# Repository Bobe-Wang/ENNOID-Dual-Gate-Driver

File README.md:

# ENNOID - Dual Gate Driver

The "Dual Gate Driver" can be directly connected to this control board:

https://github.com/paltatech/VESC-controller

The driver is pin compatible with several power modules such as the ones listed below:

- http://www.mitsubishielectric.com/semiconductors/content/product/powermod/powmod/igbtmod/tgatef/cm300du-12f_e.pdf
- https://www.wolfspeed.com/cas120m12bm2

## V0.1 (untested & archived):

V0.1 is based upon the design from wolfspeed two-channel gate driver for 1200V SiC MOSFET power modules
- https://www.wolfspeed.com/cgd15hb62p1

Feature:

- Dual gate driver
- 2W Isolated power supply / gate
- Direct mount low inductance design
- Short circuit protection
- Under voltage protection

Changes from the original wolfspeed design:

- Added Voltage sense circuit (Experimental)
- 98 x 60 mm 2 layer PCB made with Kicad
- Current sensor connector
- Temperature sensor circuit & connector
- Minimum SMD 0805 components size for easy handsoldering
- 2x8 (16) pins headers for easy connection with VESC board

## V0.2:

V0.2 is based upon the design from tiduc70a.pdf.

- http://www.ti.com/lit/ug/tiduc70a/tiduc70a.pdf

Changes from V0.1 include:

- BJT based powerstage instead of mosfet IC IXD-609
- Adjustable soft turnoff feature
- SMD gate resistor instead of MELF
- Active clamping / Over voltage protection
- Shoot trough EMI protection on PWM input

BOM link for 3 boards at Mouser below : 
- https://www.mouser.com/ProjectManager/ProjectDetail.aspx?AccessID=f6574b98ce

### Schematics

### Top View

### Bottom View

### Board View

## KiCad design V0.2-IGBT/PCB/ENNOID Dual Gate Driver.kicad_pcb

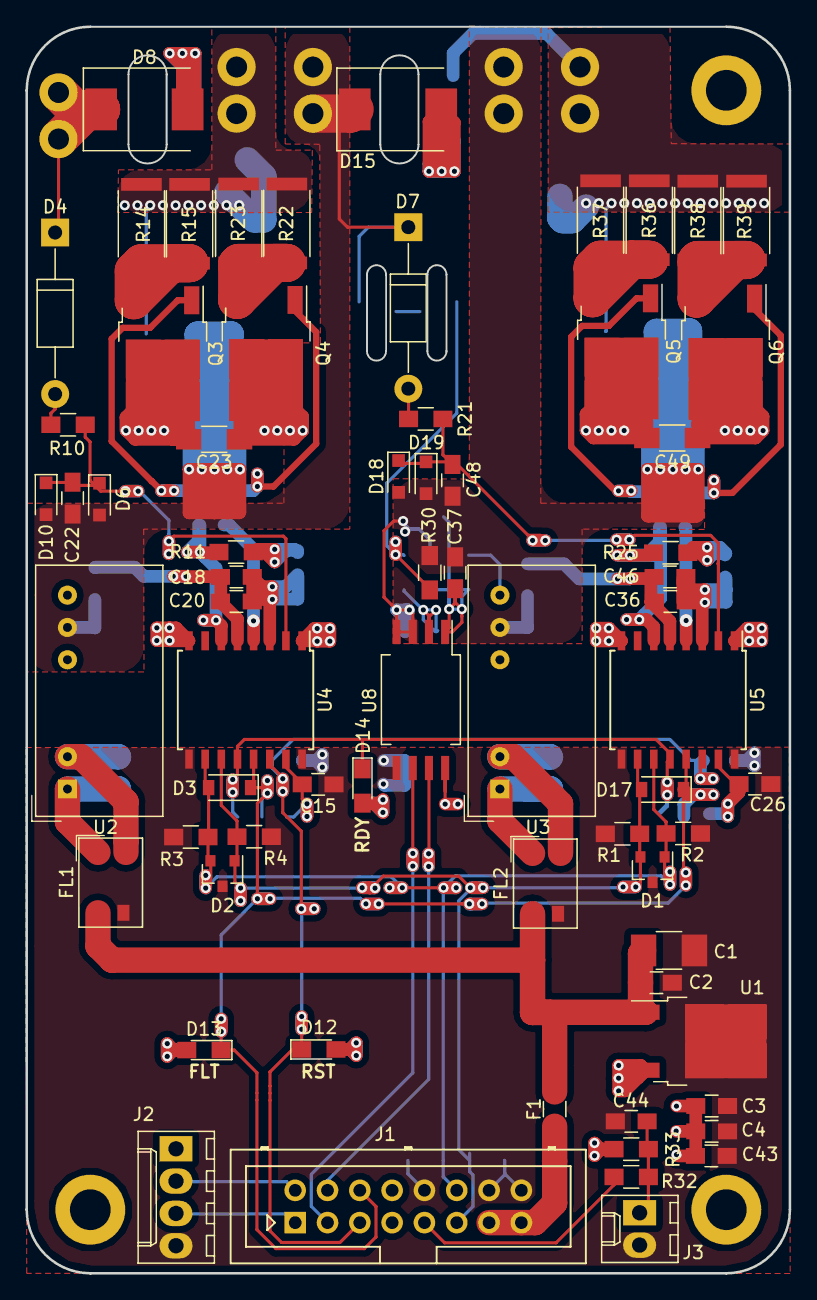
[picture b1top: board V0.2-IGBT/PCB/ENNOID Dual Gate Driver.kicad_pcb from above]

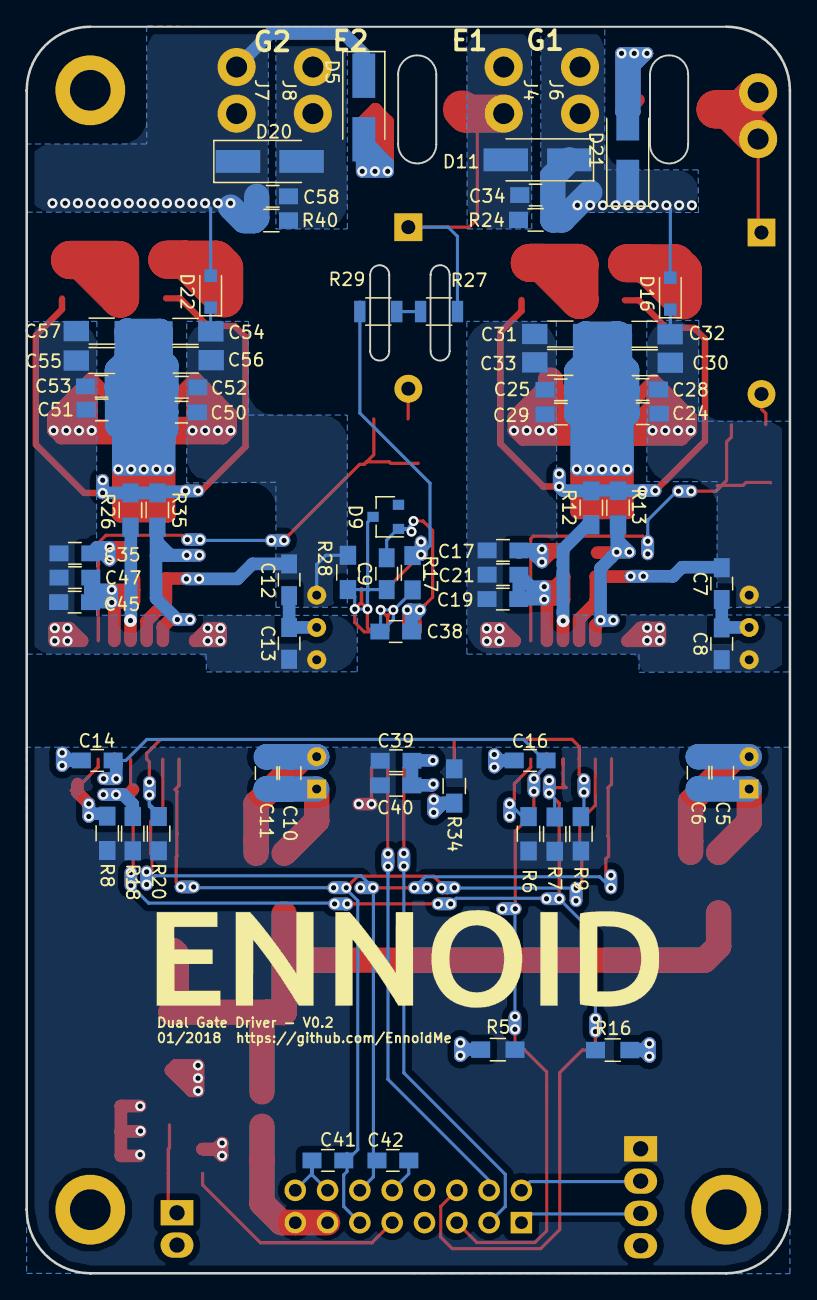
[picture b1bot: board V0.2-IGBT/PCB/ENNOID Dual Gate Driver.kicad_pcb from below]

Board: 2 copper layers, 60.0 x 98.0 mm, 142 parts (71 on the bottom side), 57 nets.

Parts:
C1: 10u; C_1210_HandSoldering
C2, C3, C5, C10, C14, C15, C16, C18, C19, C24, C25, C26, C36, C37, C39, C41, C42, C45, C50, C51: 100n; C_0805_HandSoldering
C4, C6, C7, C8, C11, C12, C13, C20, C21, C28, C29, C43, C44, C46, C47, C52, C53: 1u; C_0805_HandSoldering
C9: 10u; C_0805_HandSoldering
C17, C35: 15n; C_0805_HandSoldering
C22, C48: 220p; C_0805_HandSoldering
C23, C30, C31, C32, C33, C49, C54, C55, C56, C57: 10u; C_1206_HandSoldering
C34, C58: 0.22u; C_0805_HandSoldering
C38: 330p; C_0805_HandSoldering
C40: 2.2u; C_0805_HandSoldering
D1, D2: GSOT03C; SOT-23
D3, D17: 1N4148W; D_SOD-123
D4, D7: sTth112; D_DO-41_SOD81_P12.70mm_Horizontal
D5, D21: es2j-ltp; D_SMA_Handsoldering
D6, D18: MMSZ5242BS; D_SOD-323_HandSoldering
D8, D15: smcj440ca; D_SMC
D9: 5V; D_SOT-23_ANK
D10, D19: BAT54WS-7-F; D_SOD-323_HandSoldering
D11, D20: SMAJ18CA; D_SMA_Handsoldering
D12, D13, D14: LED; LED_0805_HandSoldering
D16, D22: PMEG4010; D_SOD-323_HandSoldering
F1: Fuse; R_0805_HandSoldering
FL1, FL2: ACM4520
G1: Logo_ENNOID; ENNOID-LOGO
J1: Conn_02x08_Odd_Even; Multicomp_MC9A12-1634_2x08x2.54mm_Straight
J2: Current; Molex_KK-6410-04_04x2.54mm_Straight
J3: TEMP; Molex_KK-6410-02_02x2.54mm_Straight
J4: PHASE; Quick_fit_terminal
J5: Collector; Quick_fit_terminal
J6: Gate_H; Quick_fit_terminal
J7: G_L; Quick_fit_terminal
J8: E; Quick_fit_terminal
J9: Mounting hole 1; MountingHole_3.2mm_M3_ISO14580_Pad
J10: Mounting Hole 2; MountingHole_3.2mm_M3_ISO14580_Pad
J11: Mounting Hole 3; MountingHole_3.2mm_M3_ISO14580_Pad
Q3, Q5: MJD3055T4G; TO-252-2
Q4, Q6: MJD2955T4G; TO-252-2
R1, R3: 4.7k; R_0805_HandSoldering
R2, R4, R10, R21, R30: 1k; R_0805_HandSoldering
R5, R16, R34: 300; R_0805_HandSoldering
R6, R8, R17: 10; R_0805_HandSoldering
R7, R9, R18, R20, R24, R40: 10k; R_0805_HandSoldering
R11, R12, R13, R25, R26, R35: 12; R_0805_HandSoldering
R14, R15, R22, R23, R36, R37, R38, R39: 3; R_2512
R27, R29: 1M; R_1206
R28: 800; R_0805_HandSoldering
R32, R33: R; R_0805_HandSoldering
U1: MC7805; TO-252-2
U2, U3: MGJ2; DCDC-Conv_muRata_MGJ2
U4, U5: ISO5852SDWR; SOIC-16W_7.5x10.3mm_Pitch1.27mm
U8: AMC1301; SSO-8_6.8x5.9mm_Pitch1.27mm_Clearance8mm

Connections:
+5V: C3.1, C4.1, C39.1, C40.1, C43.1, J2.1, R5.1, R6.2, R7.1, R8.2, R9.1, R16.1, R18.1, R20.1, R33.1, R34.1, U1.3, U8.8
+24V: C1.1, C2.1, F1.2, FL1.1, FL2.1, U1.1
/GD_HIGH/+VCC: C7.1, C18.1, C20.1, C23.1, C24.1, C28.1, C30.1, C32.1, D16.1, Q3.2, U2.7, U4.5
/GD_HIGH/-VEE: C8.2, C17.2, C19.2, C21.2, C23.2, C25.2, C29.2, C31.2, C33.2, Q4.2, U2.5, U4.1, U4.8
/GD_HIGH/C: D4.1, D8.1, J5.1
/GD_HIGH/G: C34.1, D11.1, D16.2, D21.1, J6.1, R14.1, R15.1, R22.1, R23.1, R24.2
/GD_LOW/+VCC: C12.1, C36.1, C46.1, C49.1, C50.1, C52.1, C54.1, C56.1, D22.1, Q5.2, R28.2, U3.7, U5.5
/GD_LOW/-VEE: C13.2, C35.2, C45.2, C47.2, C49.2, C51.2, C53.2, C55.2, C57.2, Q6.2, U3.5, U5.1, U5.8
/GD_LOW/G: C58.1, D5.1, D20.1, D22.2, J7.1, R36.1, R37.1, R38.1, R39.1, R40.2
/ISO_PSU_LOW/COM: C9.2, C12.2, C13.1, C37.2, C38.2, C48.2, C50.2, C51.1, C52.2, C53.1, C54.2, C55.1, C56.2, C57.1, C58.2, D9.2, D18.2, D19.2, D20.2, J8.1, R30.1, R40.1, U3.6, U8.3, U8.4
FLT: D3.1, D13.1, D17.1, J1.6, R7.2, R18.2, U4.13, U5.13
GND: C1.2, C2.2, C3.2, C4.2, C14.2, C15.1, C16.2, C26.1, C39.2, C40.2, C41.2, C42.2, C43.2, C44.2, D1.3, D2.3, FL1.2, FL2.2, J1.10, J1.14, J1.16, J2.4, J3.2, R1.2, R2.2, R3.2, R4.2, U1.2, U4.9, U4.16, U5.9, U5.16, U8.5
I+: J1.2, J2.2
I-: J1.1, J2.3
unnamed: C5.1, C6.1, FL1.4, U2.1
unnamed: C5.2, C6.2, FL1.3, U2.2
unnamed: C10.1, C11.1, FL2.4, U3.1
unnamed: C10.2, C11.2, FL2.3, U3.2
unnamed: C15.2, R6.1, U4.15
unnamed: C17.1, R11.1
unnamed: C18.2, C19.1, C20.2, C21.1, U4.3
unnamed: C22.1, D6.1, D10.1, R10.2, U4.2
unnamed: C26.2, R8.1, U5.15
unnamed: C35.1, R25.1
unnamed: C36.2, C45.1, C46.2, C47.1, U5.3
unnamed: C9.1, C37.1, D9.1, R28.1, U8.1
unnamed: C38.1, R17.2, U8.2
unnamed: C44.1, J3.1, R32.1, R33.2
unnamed: C48.1, D18.1, D19.1, R21.2, U5.2
unnamed: D4.2, R10.1
unnamed: D7.2, R21.1
unnamed: D12.2, R5.2
unnamed: D13.2, R16.2
unnamed: D14.2, R34.2
unnamed: D5.2, D15.2
unnamed: D8.2, D21.2
unnamed: F1.1, J1.13, J1.15
unnamed: Q3.1, Q4.1, R12.1, R13.1
unnamed: Q3.3, R14.2, R15.2
unnamed: Q4.3, R22.2, R23.2
unnamed: Q5.1, Q6.1, R26.1, R35.1
unnamed: Q5.3, R36.2, R37.2
unnamed: Q6.3, R38.2, R39.2
unnamed: R11.2, R13.2, U4.6
unnamed: R12.2, U4.4
unnamed: R17.1, R29.1, R30.2
unnamed: R25.2, R35.2, U5.6
unnamed: R26.2, U5.4
unnamed: R27.1, R29.2
PHASE: C7.2, C8.1, C22.2, C24.2, C25.1, C28.2, C29.1, C30.2, C31.1, C32.2, C33.1, C34.2, D6.2, D7.1, D10.2, D11.2, D15.1, J4.1, R24.1, R27.2, U2.6
PWM_H: C42.1, D1.1, D2.2, D3.2, J1.12, R2.1, R3.1, U4.10, U5.11
PWM_L: C41.1, D1.2, D2.1, D17.2, J1.11, R1.1, R4.1, U4.11, U5.10
RDY: D14.1, R9.2, R20.2, U4.12, U5.12
RST: C14.1, C16.1, D12.1, J1.5, U4.14, U5.14
TEMP: J1.9, R32.2
Vout+: J1.4, U8.7
Vout-: J1.3, U8.6

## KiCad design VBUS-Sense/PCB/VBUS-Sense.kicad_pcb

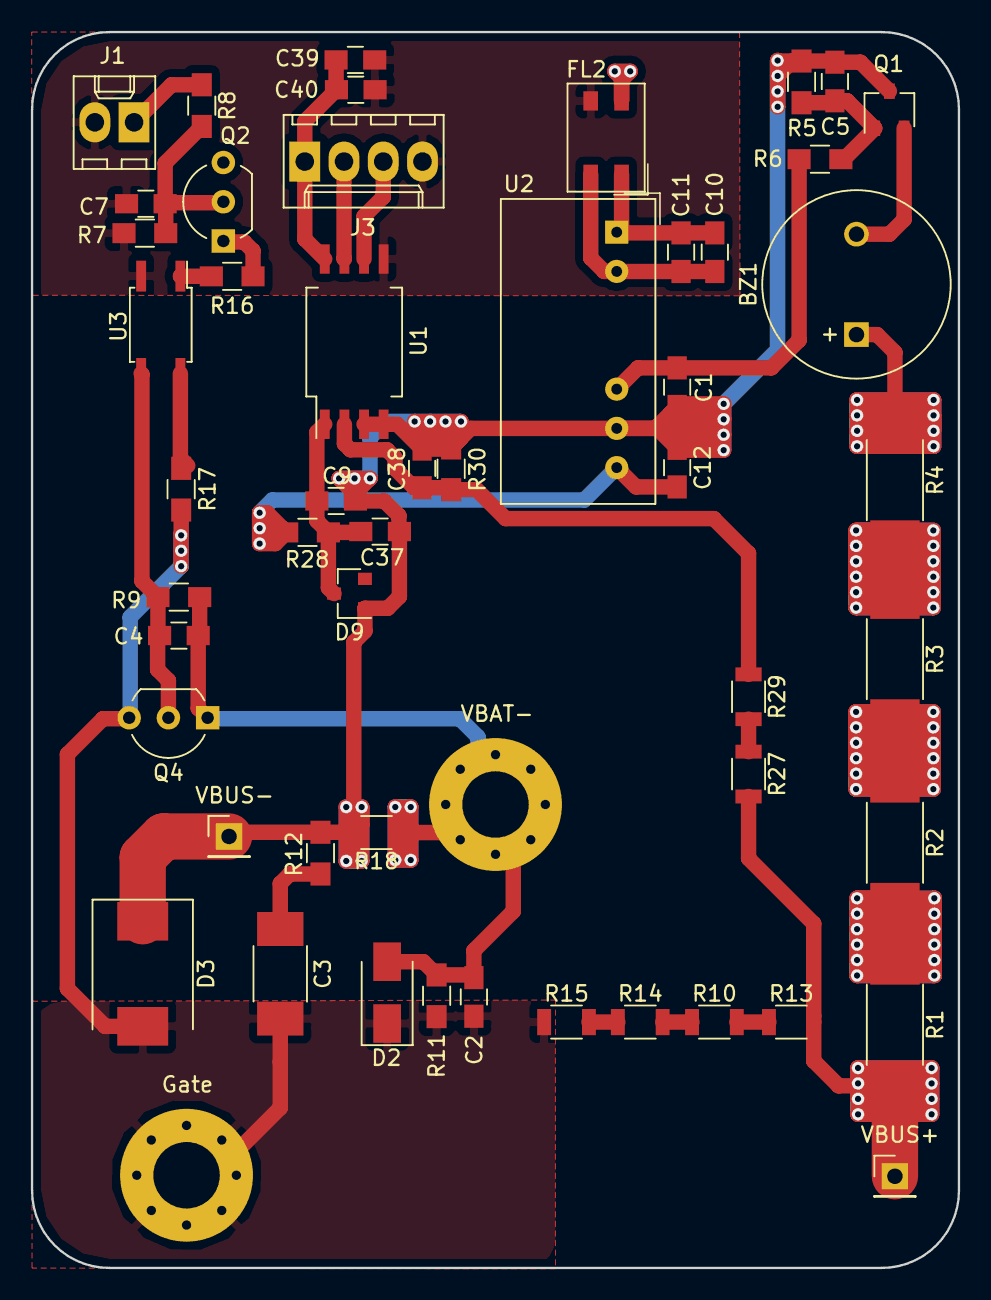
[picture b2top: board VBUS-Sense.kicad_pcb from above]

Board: 2 copper layers, 60.0 x 80.0 mm, 54 parts (1 on the bottom side), 31 nets.

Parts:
BZ1: Buzzer; MagneticBuzzer_ProSignal_ABT-410-RC
C1, C11, C12: 1u; C_0805_HandSoldering
C2: 0.15u; C_0805_HandSoldering
C3: 0.15u; C_1812_HandSoldering
C4, C5, C7, C10, C37, C39: 100n; C_0805_HandSoldering
C9: 10u; C_0805_HandSoldering
C38: 330p; C_0805_HandSoldering
C40: 2.2u; C_0805_HandSoldering
D2: D_Zener 18V SMAJ18CA; D_SMA
D3: D_Zener 440v SMJC440CA; D_SMC
D9: 5V; D_SOT-23_ANK
FL2: ACM4520
J1: Conn_01x02 to external 12V power switch or VESC G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; Molex_KK-6410-02_02x2.54mm_Straight
J3: Conn_01x04 to vesc board; Molex_KK-6410-04_04x2.54mm_Straight
LOGO1: Logo_ENNOID; ENNOID-LOGO
MK1: VBUS-; Pin_Header_Straight_1x01_Pitch2.54mm
MK2: VBUS+; Pin_Header_Straight_1x01_Pitch2.54mm
MK3: Gate; MountingHole_4.3mm_M4_Pad_Via
MK4: VBAT-; MountingHole_4.3mm_M4_Pad_Via
Q1: Depletion mode FET ex: CPC3982; SOT-23W
Q2, Q4: 2N7000; TO-92_Inline_Wide
R1, R2, R3, R4: 7.5K; R_2512_HandSoldering
R5: 20k; R_0805_HandSoldering
R6: 100; R_0805_HandSoldering
R7: 1M; R_0805_HandSoldering
R8, R12, R16, R17, R30: 1k; R_0805_HandSoldering
R9: 10k; R_0805_HandSoldering
R10, R13, R14, R15, R18: 200k; R_1206
R11: 30k; R_0805_HandSoldering
R27, R29: 1M; R_1206
R28: 800; R_0805_HandSoldering
U1: AMC1301; SSO-8_6.8x5.9mm_Pitch1.27mm_Clearance8mm
U2: MGJ2; DCDC-Conv_muRata_MGJ2
U3: LTV-356T; SO-4_4.4x3.6mm_Pitch2.54mm

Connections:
+5V: C39.1, C40.1, FL2.1, J3.1, Q2.3, U1.8
/ISO_PSU/+VCC: C12.1, R28.2, U2.7
/ISO_PSU/-VEE: C1.2, R6.2, U2.5
/ISO_PSU/COM: C1.1, C5.2, C9.2, C12.2, C37.2, C38.2, D3.1, D9.2, MK1.1, Q1.3, R5.1, R12.1, R18.2, R30.1, U1.3, U1.4, U2.6
/Inrush_Limiter/+VBUS: MK2.1, R1.2, R13.2, R27.2
/Inrush_Limiter/GATE: C2.1, C3.2, D2.1, D3.2, MK3.1, Q4.3, R11.2, R15.1, R17.2
/Inrush_Limiter/ON/OFF: J1.1, R8.2
/Inrush_Limiter/VBAT-: C2.2, C4.2, D2.2, MK4.1, Q4.1, R9.1, R11.1, R18.1
/V_BUS/Vout+: J3.2, U1.7
/V_BUS/Vout-: J3.3, U1.6
GND: C7.2, C39.2, C40.2, FL2.2, J1.2, J3.4, R7.2, U1.5, U3.2
unnamed: BZ1.1, R4.1
unnamed: BZ1.2, Q1.2
unnamed: C3.1, R12.2
unnamed: C4.1, Q4.2, R9.2, U3.3
unnamed: C5.1, Q1.1, R5.2, R6.1
unnamed: C7.1, Q2.2, R7.1, R8.1
unnamed: C10.1, C11.1, FL2.4, U2.1
unnamed: C10.2, C11.2, FL2.3, U2.2
unnamed: C9.1, C37.1, D9.1, R28.1, U1.1
unnamed: C38.1, R29.1, R30.2, U1.2
unnamed: Q2.1, R16.2
unnamed: R1.1, R2.2
unnamed: R2.1, R3.2
unnamed: R3.1, R4.2
unnamed: R10.1, R14.2
unnamed: R10.2, R13.1
unnamed: R14.1, R15.2
unnamed: R16.1, U3.1
unnamed: R17.1, U3.4
unnamed: R27.1, R29.2

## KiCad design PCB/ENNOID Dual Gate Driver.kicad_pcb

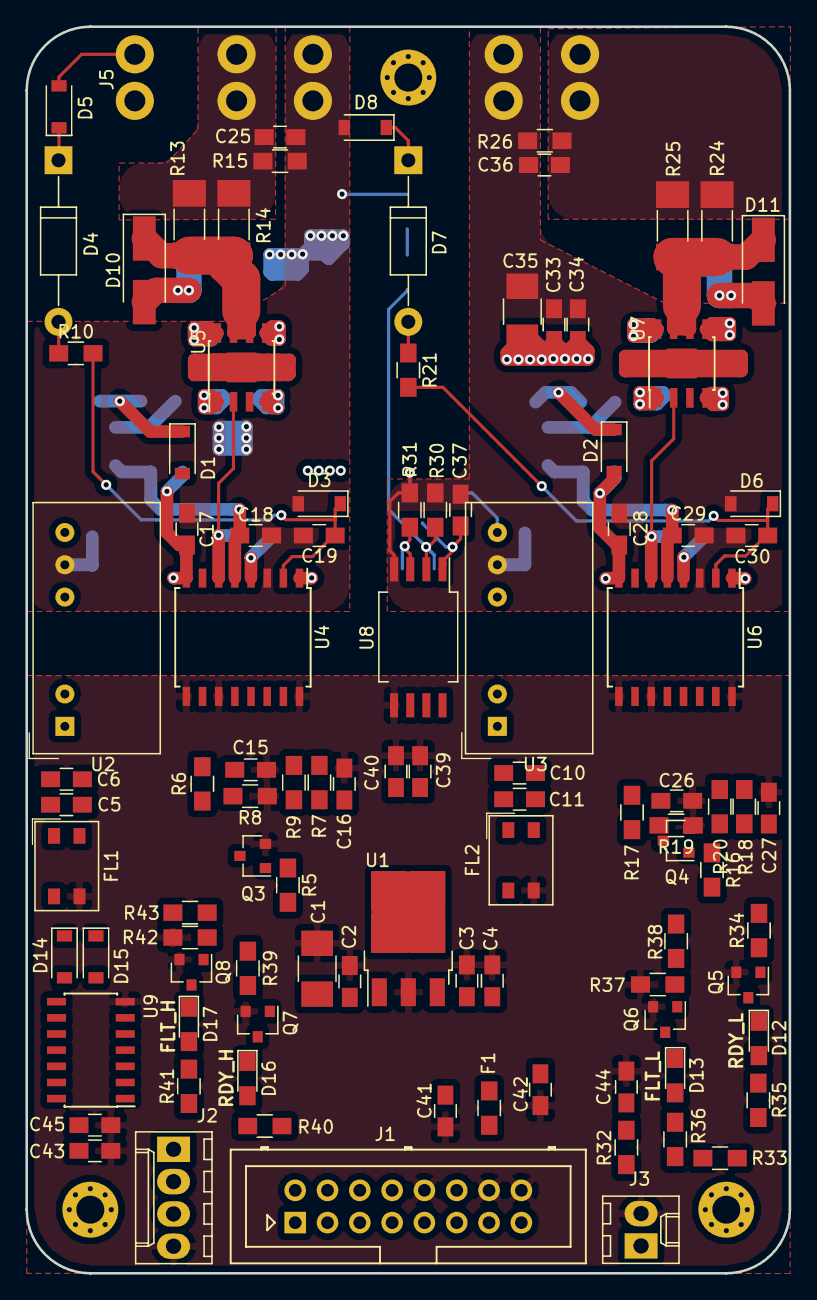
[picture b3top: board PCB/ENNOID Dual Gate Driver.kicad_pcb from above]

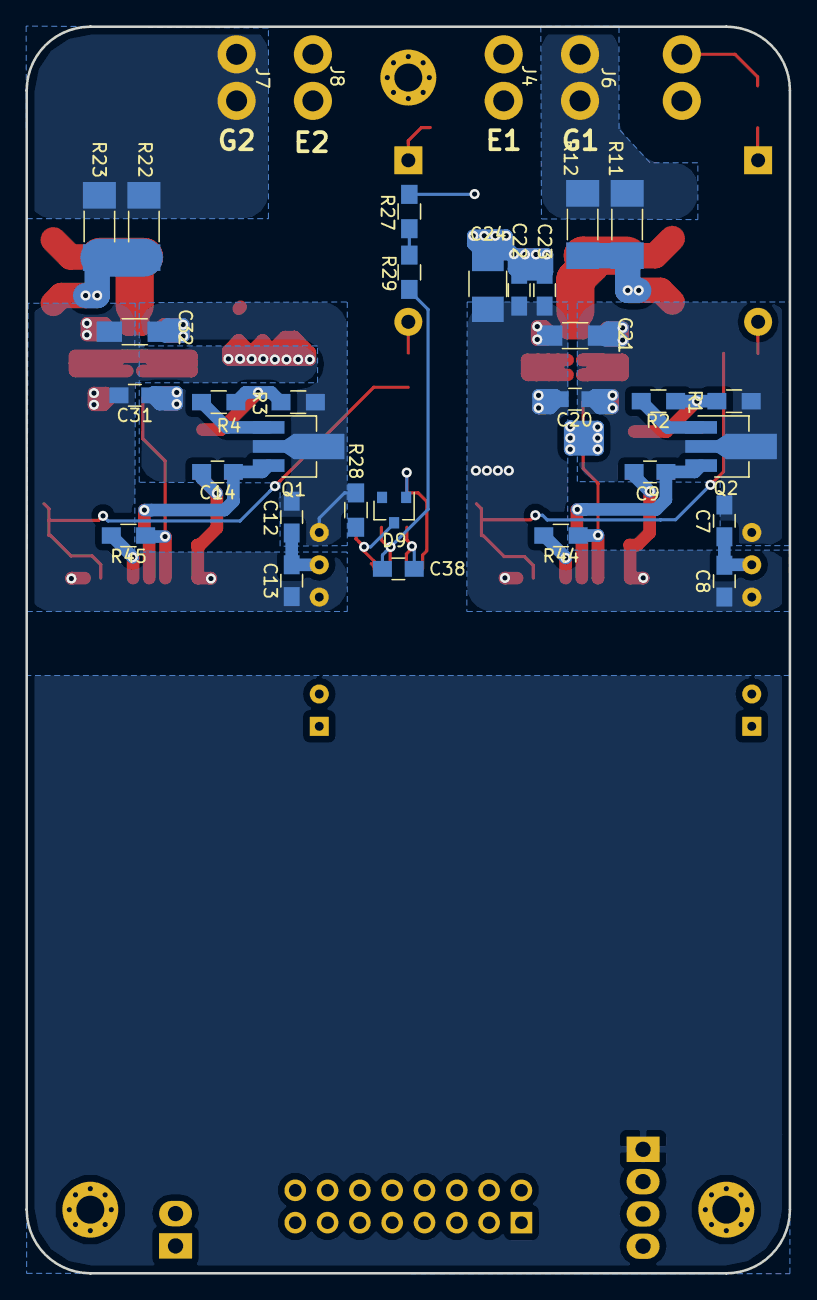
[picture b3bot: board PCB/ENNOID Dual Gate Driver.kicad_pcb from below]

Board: 2 copper layers, 60.0 x 98.0 mm, 138 parts (34 on the bottom side), 75 nets.

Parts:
C1: 10u; C_1210_HandSoldering
C2, C3, C5, C10, C15, C16, C17, C18, C20, C23, C26, C27, C28, C29, C31, C34, C37, C39, C41, C42, C45: 100n; C_0805_HandSoldering
C4, C6, C7, C8, C9, C11, C12, C13, C14, C43, C44: 1u; C_0805_HandSoldering
C19, C25, C30, C36: DNP; C_0805_HandSoldering
C21, C32: 4.7u; C_1206_HandSoldering
C22, C33: 10n; C_0805_HandSoldering
C24, C35: 10u; R_1210_HandSoldering
C38: 330p; C_0805_HandSoldering
C40: 2.2u; C_0805_HandSoldering
D1, D2: MMSZ5251B; D_SOD-123
D3, D5, D6, D8: D_Zener; D_SOD-123
D4, D7: D; D_DO-41_SOD81_P12.70mm_Horizontal
D9: 5V; D_SOT-23_ANK
D10, D11: D; D_SMA_Handsoldering
D12, D13, D16, D17: LED; LED_0805_HandSoldering
D14, D15: B140HW; D_SOD-123
F1: Fuse; R_0805_HandSoldering
FL1, FL2: ACM4520
J1: Conn_02x08_Odd_Even; Multicomp_MC9A12-1634_2x08x2.54mm_Straight
J2: Current; Molex_KK-6410-04_04x2.54mm_Straight
J3: TEMP; Molex_KK-6410-02_02x2.54mm_Straight
J4: PHASE; Quick_fit_terminal
J5: Collector; Quick_fit_terminal
J6: Gate_H; Quick_fit_terminal
J7: G_L; Quick_fit_terminal
J8: E; Quick_fit_terminal
M1, M2, M3: MountingHole_2.2mm_M2_Pad_Via
Q1, Q2: Q_NPN_BCE; SOT-89-3_Handsoldering
Q3, Q4: 2N7002K-7; SOT-23
Q5, Q6, Q7, Q8: 2N7002; SOT-23
R1, R3, R7, R9, R10, R18, R20, R21, R37, R42: 10k; R_0805_HandSoldering
R2, R4: 0; R_0805_HandSoldering
R5, R6, R16, R17, R30, R31: 1k; R_0805_HandSoldering
R8, R15, R19, R26: 47k; R_0805_HandSoldering
R11, R12, R22, R23: DND; R_MELF_MMB-0207
R13, R14, R24, R25: 20; R_MELF_MMB-0207
R27, R29: 1M; R_0805_HandSoldering
R28: 200; R_0805_HandSoldering
R32, R33: R; R_0805_HandSoldering
R34, R39: 4.12k10; R_0805_HandSoldering
R35, R36, R40, R41: 4.12k; R_0805_HandSoldering
R38, R43: 10; R_0805_HandSoldering
R44, R45: DNP; R_0805_HandSoldering
U1: MC7805; TO-252-3_TabPin2
U2, U3: MGJ2; DCDC-Conv_muRata_MGJ2
U4, U6: 1ED020I12-F2; SOIC-16W_7.5x10.3mm_Pitch1.27mm
U5, U7: IXD-609; SOIC-8-1EP_3.9x4.9mm_Pitch1.27mm
U8: AMC1301; SSO-8_6.8x5.9mm_Pitch1.27mm_Clearance8mm
U9: 4069; SOIC-14_3.9x8.7mm_Pitch1.27mm

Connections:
+5V: C3.1, C4.1, C16.1, C27.1, C39.1, C40.1, C43.1, C45.1, J2.1, R7.1, R9.1, R18.1, R20.1, R33.1, U1.3, U4.15, U6.15, U8.8, U9.14
/GD_HIGH/+VCC: C7.1, C20.1, C21.1, Q2.2, R1.2, U2.7, U5.1, U5.8
/GD_HIGH/-VEE: C8.2, C9.2, C17.1, C20.2, C21.2, C22.2, C23.2, C24.2, D1.2, U2.5, U4.1, U4.8, U5.4, U5.5
/GD_HIGH/C: D5.2, J5.1
/GD_HIGH/G: C25.1, J6.1, R11.2, R12.2, R13.2, R14.2, R15.1
/GD_HIGH/VCC_REG: C9.1, C18.2, Q2.3, U4.5
/GD_LOW/+VCC: C12.1, C31.1, C32.1, Q1.2, R3.2, R28.2, U3.7, U7.1, U7.8
/GD_LOW/-VEE: C13.2, C14.2, C28.1, C31.2, C32.2, C33.2, C34.2, C35.2, D2.2, U3.5, U6.1, U6.8, U7.4, U7.5
/GD_LOW/E: C12.2, C13.1, C28.2, C29.1, C30.2, C33.1, C34.1, C35.1, C36.2, C37.2, D6.2, D9.2, J8.1, R26.2, R30.1, R31.1, U3.6, U6.3, U8.4
/GD_LOW/G: C36.1, J7.1, R22.2, R23.2, R24.2, R25.2, R26.1
/GD_LOW/VCC_REG: C14.1, C29.2, Q1.3, U6.5
FLT_ALL: D14.1, D15.1, J1.6, R5.2, R16.2
FLT_H: R7.2, U4.13, U9.3, U9.9
FLT_L: R18.2, U6.13, U9.1, U9.5
GND: C1.2, C2.2, C3.2, C4.2, C15.2, C16.2, C26.2, C27.2, C39.2, C40.2, C41.2, C42.2, C43.2, C44.2, C45.2, FL1.2, FL2.2, J1.10, J1.14, J1.16, J2.4, J3.2, Q3.2, Q4.2, Q5.2, Q6.2, Q7.2, Q8.2, R8.1, R19.1, R37.1, R42.1, U1.2, U4.9, U4.11, U4.16, U6.9, U6.11, U6.16, U8.5, U9.7
I+: J1.2, J2.2
I-: J1.1, J2.3
unnamed: C5.1, C6.1, FL1.4, U2.1
unnamed: C5.2, C6.2, FL1.3, U2.2
unnamed: C10.1, C11.1, FL2.4, U3.1
unnamed: C10.2, C11.2, FL2.3, U3.2
unnamed: C15.1, Q3.3, R6.1, R8.2, U4.10
unnamed: C19.1, D3.1, R10.2, U4.2
unnamed: C26.1, Q4.3, R17.1, R19.2, U6.10
unnamed: C30.1, D6.1, R21.2, U6.2
unnamed: C37.1, D9.1, R28.1, U8.1
unnamed: C38.1, R29.1, R30.2, U8.2
unnamed: C38.2, R31.2, U8.3
unnamed: C44.1, J3.1, R32.1, R33.2
unnamed: D1.1, R1.1, R2.1
unnamed: D2.1, R3.1, R4.1
unnamed: D4.1, D5.1
unnamed: D4.2, R10.1
unnamed: D7.1, D8.1
unnamed: D7.2, R21.1
unnamed: D10.1, R13.1, R14.1, U5.6, U5.7
unnamed: D10.2, R11.1, R12.1
unnamed: D11.1, R24.1, R25.1, U7.6, U7.7
unnamed: D11.2, R22.1, R23.1
unnamed: D12.1, Q5.3
unnamed: D12.2, R35.2
unnamed: D13.1, Q6.3
unnamed: D13.2, R36.2
unnamed: D14.2, U9.8
unnamed: D15.2, U9.6
unnamed: D16.1, Q7.3
unnamed: D16.2, R40.2
unnamed: D17.1, Q8.3
unnamed: D17.2, R41.2
unnamed: F1.1, J1.13, J1.15
unnamed: Q1.1, R4.2
unnamed: Q2.1, R2.2
unnamed: Q3.1, R5.1
unnamed: Q4.1, R16.1
unnamed: Q5.1, R34.1
unnamed: Q6.1, R37.2, R38.2
unnamed: Q7.1, R39.1
unnamed: Q8.1, R42.2, R43.2
unnamed: R27.1, R29.2
unnamed: R38.1, U9.2
unnamed: R43.1, U9.4
unnamed: R44.1, U4.4
unnamed: R44.2, U4.6, U5.2
unnamed: R45.1, U6.4
unnamed: R45.2, U6.6, U7.2
PHASE: C7.2, C8.1, C17.2, C18.1, C19.2, C22.1, C23.1, C24.1, C25.2, D3.2, D8.2, J4.1, R15.2, R27.2, U2.6, U4.3
PWM_H: C41.1, J1.11, R6.2
PWM_L: C42.1, J1.12, R17.2
RDY_H: R9.2, R39.2, U4.12
RDY_L: R20.2, R34.2, U6.12
RST: J1.5, U4.14, U6.14
TEMP: J1.9, R32.2
VCC_IN: C1.1, C2.1, F1.2, FL1.1, FL2.1, R35.1, R36.1, R40.1, R41.1, U1.1
Vout+: J1.3, U8.7
Vout-: J1.4, U8.6

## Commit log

2017-12-13 Readme modifs
2017-12-13 Readme v2
2017-12-13 Gate power calcculation
2017-12-13 Update removing .bak & V_phase adj submodule
2017-12-13 .gitignore for kicad
2017-12-13 remove . bak
2017-12-14 Schematics & footprints completed
    Ready for PCBnew
2017-12-14 PCB half-done
2017-12-14 Readme
2017-12-16 Routing has started
2017-12-18 PCB completed with readme update
2017-12-18 Readme update
2017-12-18 Minor updates
2017-12-18 Photos updates
2017-12-18 Minor changes
2017-12-18 Small changes
2017-12-18 pcb error correction
2017-12-18 Small updates
2017-12-19 PCB changes
2017-12-27 V0.1 wolfspeed
2017-12-27 V0.1
2017-12-27 V0.2-IGBT
2017-12-27 V0.1 readme
2017-12-27 V0.2 readme
2017-12-28 v0.2 PCB
2017-12-28 Readme V0.2
2017-12-30 v0.2
2018-01-01 v0.2 PCB POWER STAGE COMPLETED
2018-01-02 v2.0 PCB SIGNAL SIDE
2018-01-02 SIGNAL PCV V0.2
2018-01-02 V0.2 PCB completed
2018-01-03 V0.2 completed
2018-01-03 Readme V0.2 & pics
2018-01-03 PCB V0.2
2018-01-03 ENNOID LOGO on V0.2
2018-01-03 logo
2018-01-04 V0.2 shoot through EMI protection added
    In response to Marcos repply to my post on endless sphere https://endless-sphere.com/forums/viewtopic.php?f=30&t=89056&start=75
2018-01-04 V0.2 Fab files
2018-01-06 VBUS sensor & voltage sense circuit changes
2018-01-06 Vsense
2018-01-08 Schematics update
2018-01-08 V0.2 BOM and schematics updated
2018-01-08 V0.2 BOM and schematics updates
2018-01-08 V0.2 pcb changes
2018-01-09 V0.2 pics update
2018-01-10 V0.3 started
2018-01-15 gitignor
2018-01-15 removed v0.3
2018-01-21 Maintenance update
2018-01-26 VBUS update
2018-01-26 PIC update
2018-01-26 BOM update
2018-01-26 VBUS-SENSE changes
2018-01-26 VBUS-SENSE
2018-01-27 VBUS sense
2018-02-05 V0.3 - New voltage clamping technique
    Added TM4 reflex active clampiing
2019-04-08 no changes
2019-06-30 Readme update no changes
